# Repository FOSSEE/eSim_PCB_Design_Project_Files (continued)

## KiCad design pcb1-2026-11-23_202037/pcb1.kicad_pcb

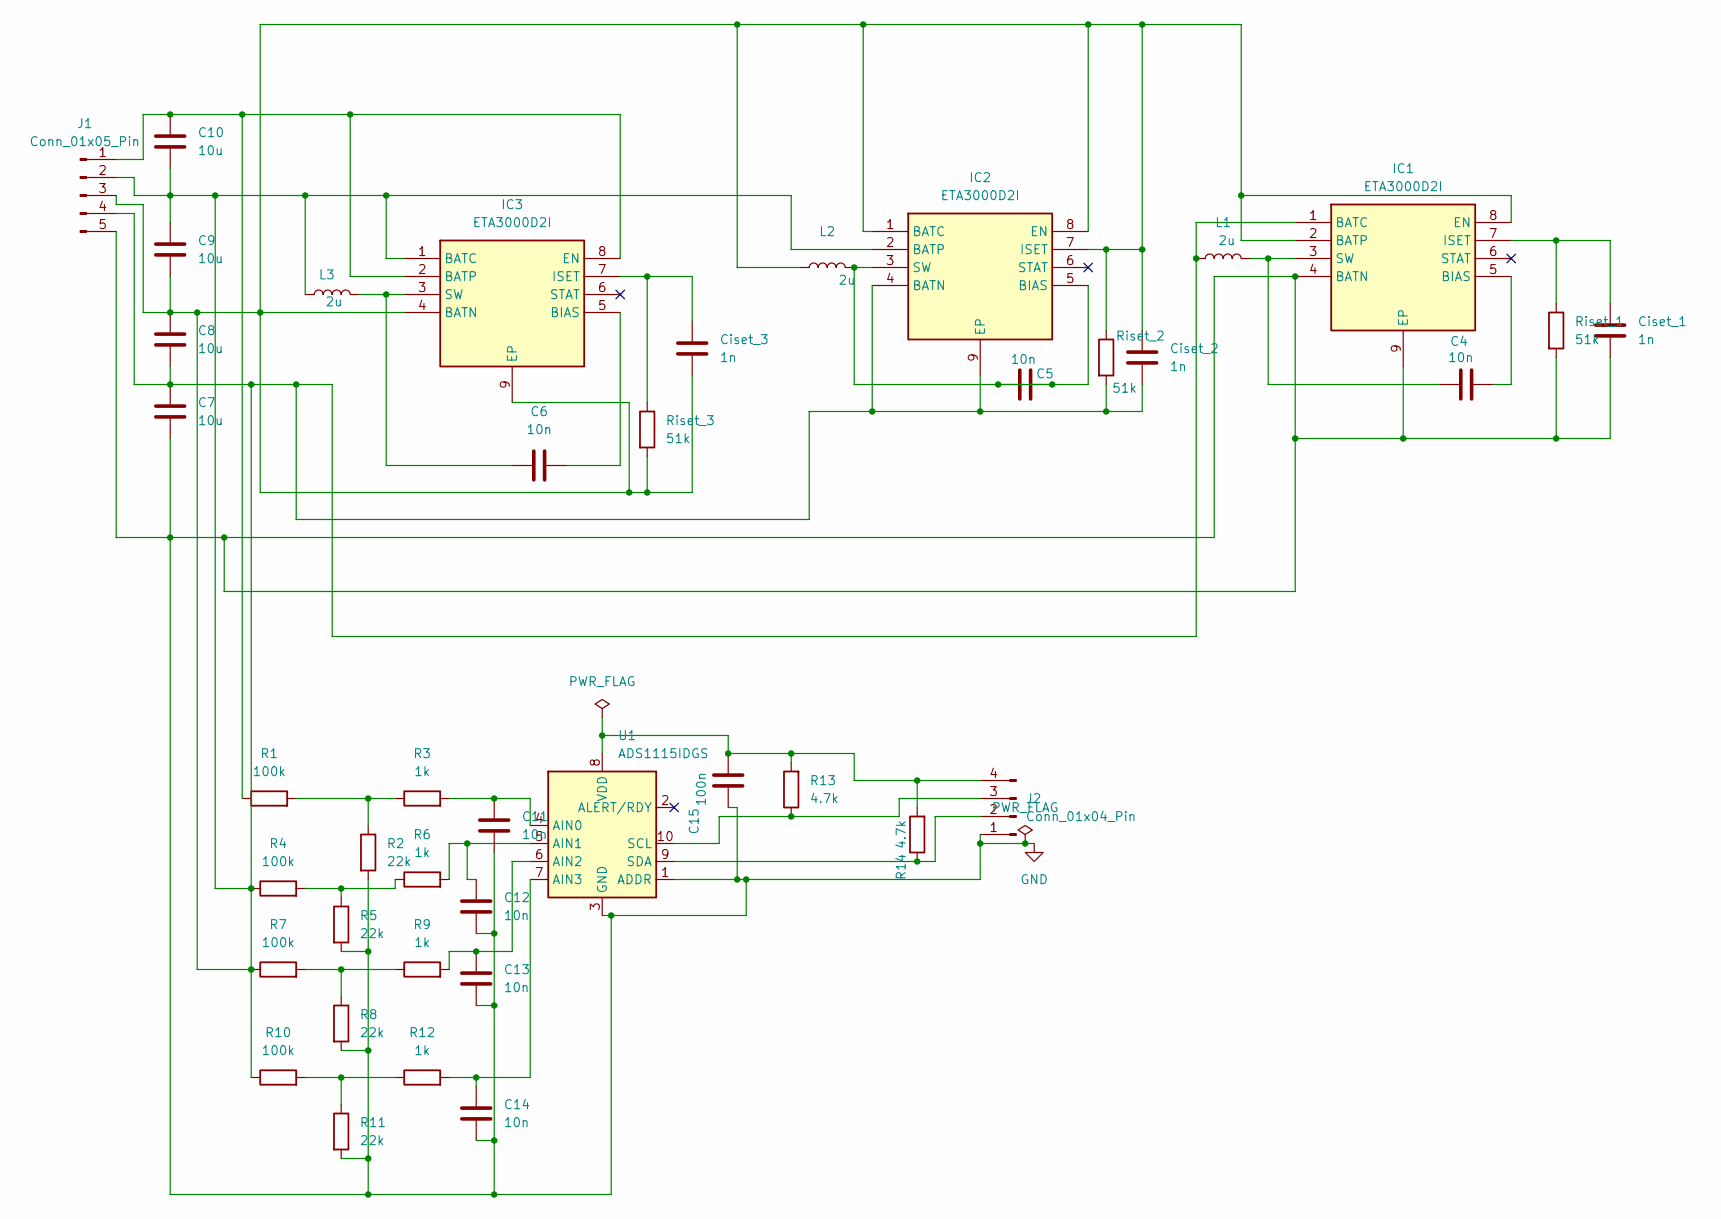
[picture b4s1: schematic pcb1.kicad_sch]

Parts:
C4, C5, C6, C11, C12, C13, C14: 10n; C_0805_2012Metric_Pad1.18x1.45mm_HandSolder
C7, C8, C9, C10: 10u; C_1206_3216Metric_Pad1.33x1.80mm_HandSolder
C15: 100n; C_0805_2012Metric_Pad1.18x1.45mm_HandSolder
Ciset_1, Ciset_2, Ciset_3: 1n; C_0805_2012Metric_Pad1.18x1.45mm_HandSolder
IC1, IC2, IC3: ETA3000D2I; DFN-8-1EP_3x3mm_P0.5mm_EP1.65x2.38mm; Manufacturer_Part_Number ETA3000D2I
J1: Conn_01x05_Pin; JST_XH_B5B-XH-A_1x05_P2.50mm_Vertical
J2: Conn_01x04_Pin; PinHeader_1x04_P2.54mm_Vertical
L1, L2, L3: 2u; L_Bourns-SRN4018
R1, R4, R7, R10: 100k; R_0805_2012Metric_Pad1.20x1.40mm_HandSolder
R2, R5, R8, R11: 22k; R_0805_2012Metric_Pad1.20x1.40mm_HandSolder
R3, R6, R9, R12: 1k; R_0805_2012Metric_Pad1.20x1.40mm_HandSolder
R13, R14: 4.7k; R_0805_2012Metric_Pad1.20x1.40mm_HandSolder
Riset_1, Riset_2, Riset_3: 51k; R_0805_2012Metric_Pad1.20x1.40mm_HandSolder
U1: ADS1115IDGS; TSSOP-10_3x3mm_P0.5mm

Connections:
GND: C7.2, C11.1, C12.1, C13.1, C14.1, C15.2, Ciset_1.1, IC1.4 (BATN), IC1.9 (EP), J1.5, J2.1, R2.2, R5.2, R8.2, R11.2, Riset_1.2, U1.1 (ADDR), U1.3 (GND)
unnamed: C7.1, C8.1, C8.2, C9.1, C9.2, C10.2, Ciset_2.1, Ciset_2.2, Ciset_3.2, IC1.1 (BATC), IC1.2 (BATP), IC1.8 (EN), IC2.1 (BATC), IC2.2 (BATP), IC2.4 (BATN), IC2.7 (ISET), IC2.8 (EN), IC2.9 (EP), IC3.1 (BATC), IC3.4 (BATN), IC3.9 (EP), J1.2, J1.3, J1.4, L1.1, L2.1, L3.1, R4.1, R7.1, R10.1, Riset_2.1, Riset_2.2, Riset_3.2
unnamed: C4.2, IC1.5 (BIAS)
unnamed: Ciset_1.2, IC1.7 (ISET), Riset_1.1
unnamed: C4.1, IC1.3 (SW), L1.2
unnamed: C5.1, C5.2, IC2.3 (SW), IC2.5 (BIAS), L2.2
unnamed: C10.1, IC3.2 (BATP), IC3.8 (EN), J1.1, R1.1
unnamed: C6.2, IC3.5 (BIAS)
unnamed: Ciset_3.1, IC3.7 (ISET), Riset_3.1
unnamed: C6.1, IC3.3 (SW), L3.2
unnamed: J2.2, R14.1, U1.9 (SDA)
unnamed: J2.3, R13.1, U1.10 (SCL)
unnamed: C15.1, J2.4, R13.2, R14.2, U1.8 (VDD)
unnamed: R1.2, R2.1, R3.1
unnamed: R4.2, R5.1, R6.1
unnamed: R7.2, R8.1, R9.1
unnamed: R10.2, R11.1, R12.1
unnamed: C11.2, R3.2, U1.4 (AIN0)
unnamed: C12.2, R6.2, U1.5 (AIN1)
unnamed: C13.2, R9.2, U1.6 (AIN2)
unnamed: C14.2, R12.2, U1.7 (AIN3)

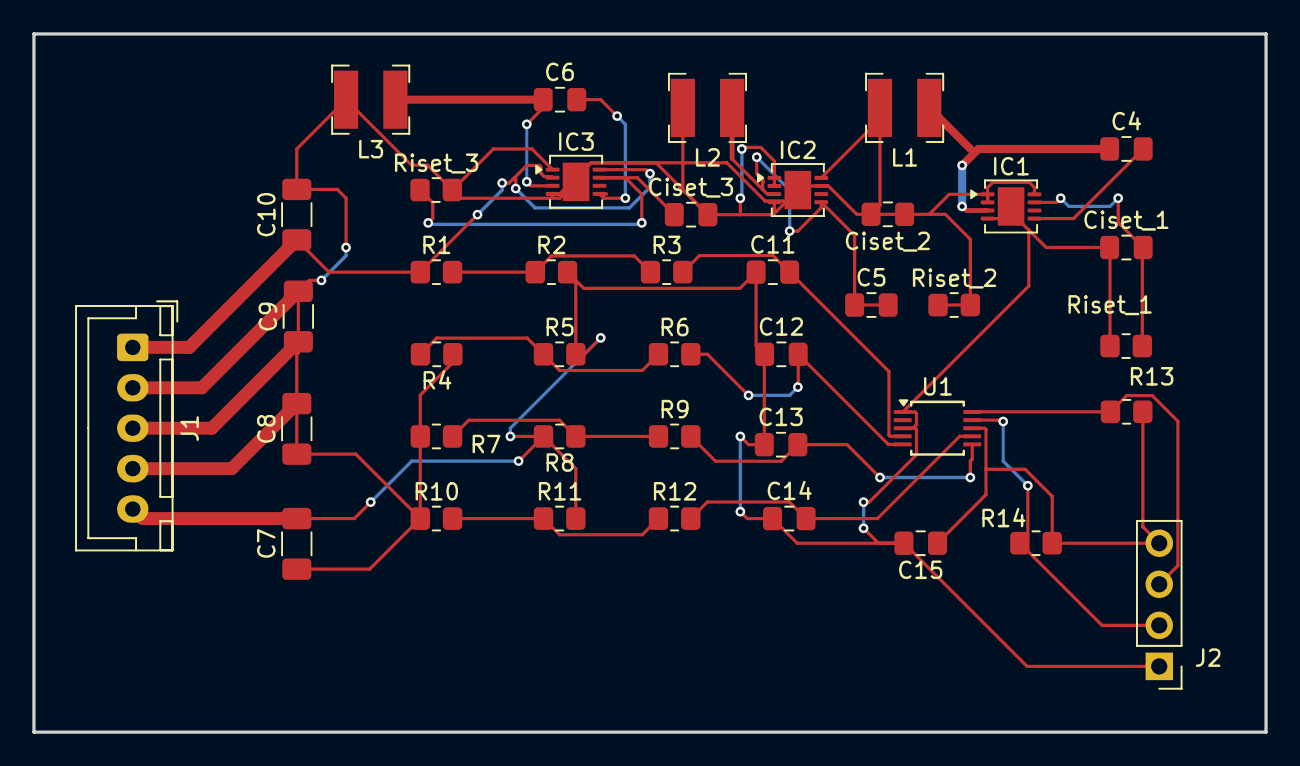
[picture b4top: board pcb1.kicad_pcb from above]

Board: 2 copper layers, 76.2 x 43.2 mm, 41 parts (0 on the bottom side), 21 nets.

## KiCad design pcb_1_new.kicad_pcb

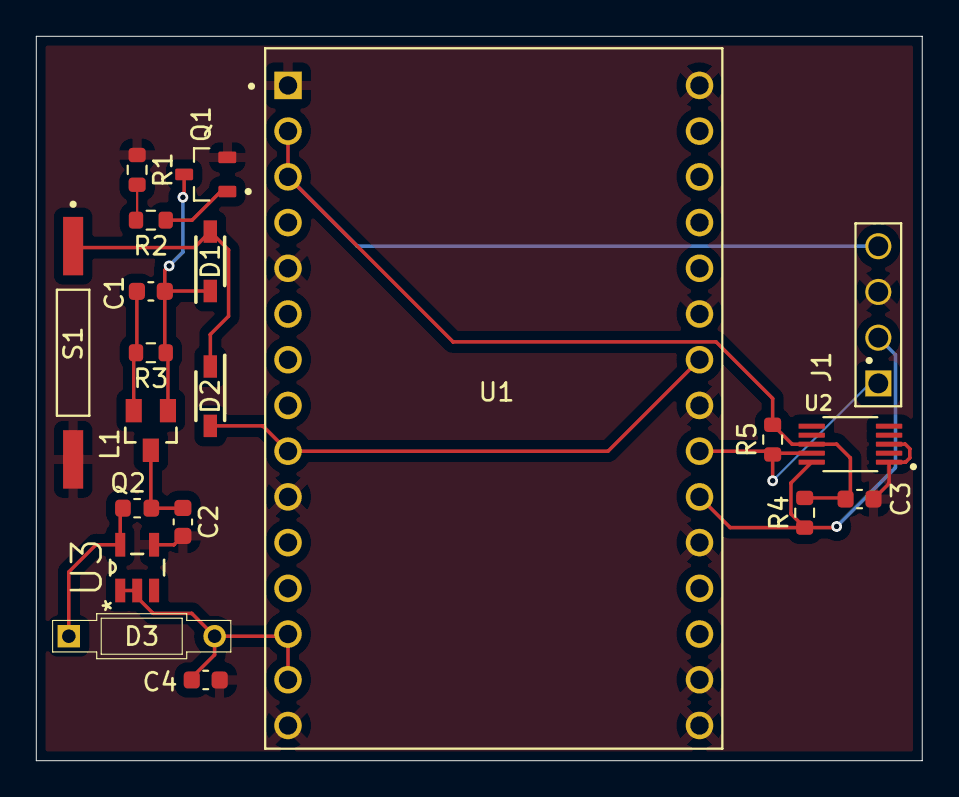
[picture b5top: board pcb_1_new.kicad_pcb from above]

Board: 2 copper layers, 49.2 x 40.2 mm, 20 parts (0 on the bottom side), 13 nets.

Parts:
C1: 100 nF; C_0603_1608Metric
C2: 10uF; C_0603_1608Metric
C3: 0.1uF; C_0603_1608Metric
C4: 47uF; C_0603_1608Metric
D1, D2: 1N4148W-7-F; SOD3716X115N
D3: 1N5711; DIOAD810W51L378D176P
J1: 61300411121; WURTH_61300411121
L1: inductor; L_0603_1608Metric
Q1: MMBT3904; TRANS_MMBT3904
Q2: IRLML6401; SOT23-3
R1, R4, R5: 10K; R_0603_1608Metric
R2: 470; R_0603_1608Metric
R3: 10k; R_0603_1608Metric
S1: MISM7R1015; SW_MISM7R1015
U1: ESP32-C3-DEVKITC-02; XCVR_ESP32-C3-DEVKITC-02
U2: ADS1114IDGSR; SOP50P490X110-10N
U3: NCP1402SN50T1G; SOT95P275X110-5N

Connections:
3V3: C3.1, J1.04, R4.2, R5.2, U1.2 (3V3), U1.3 (3V3), U2.8 (VDD)
Button state pin: D2.2, U1.9 (GPIO7), U1.24 (GPIO10)
GND: C2.2, C3.2, C4.2, J1.03, Q1.2, R1.1, S1.2, U1.1 (GND), U1.5 (GND), U1.10 (GND), U1.15 (GND), U1.16 (GND), U1.17 (GND), U1.20 (GND), U1.23 (GND), U1.25 (GND), U1.30 (GND), U2.1 (ADDR), U2.3 (GND), U3.4 (GND)
unnamed: C1.2, D1.1, Q1.3, Q2.1, R3.1
unnamed: D1.2, D2.1, S1.1
unnamed: D3.1, L1.2, U3.5 (LX)
unnamed: Q1.1, R2.1
POwer hold pin: R1.2, R2.2
SCL: J1.02, R4.1, U1.21 (GPIO21/U0TXD), U2.10 (SCL)
SDA: J1.01, R5.1, U1.22 (GPIO20/U0RXD), U2.9 (SDA)
V5_reg: C4.1, D3.2, U1.13 (5V), U1.14 (5V), U3.1 (CE), U3.2 (OUT)
Vcc: C2.1, L1.1, Q2.3
Vin: C1.1, Q2.2, R3.2

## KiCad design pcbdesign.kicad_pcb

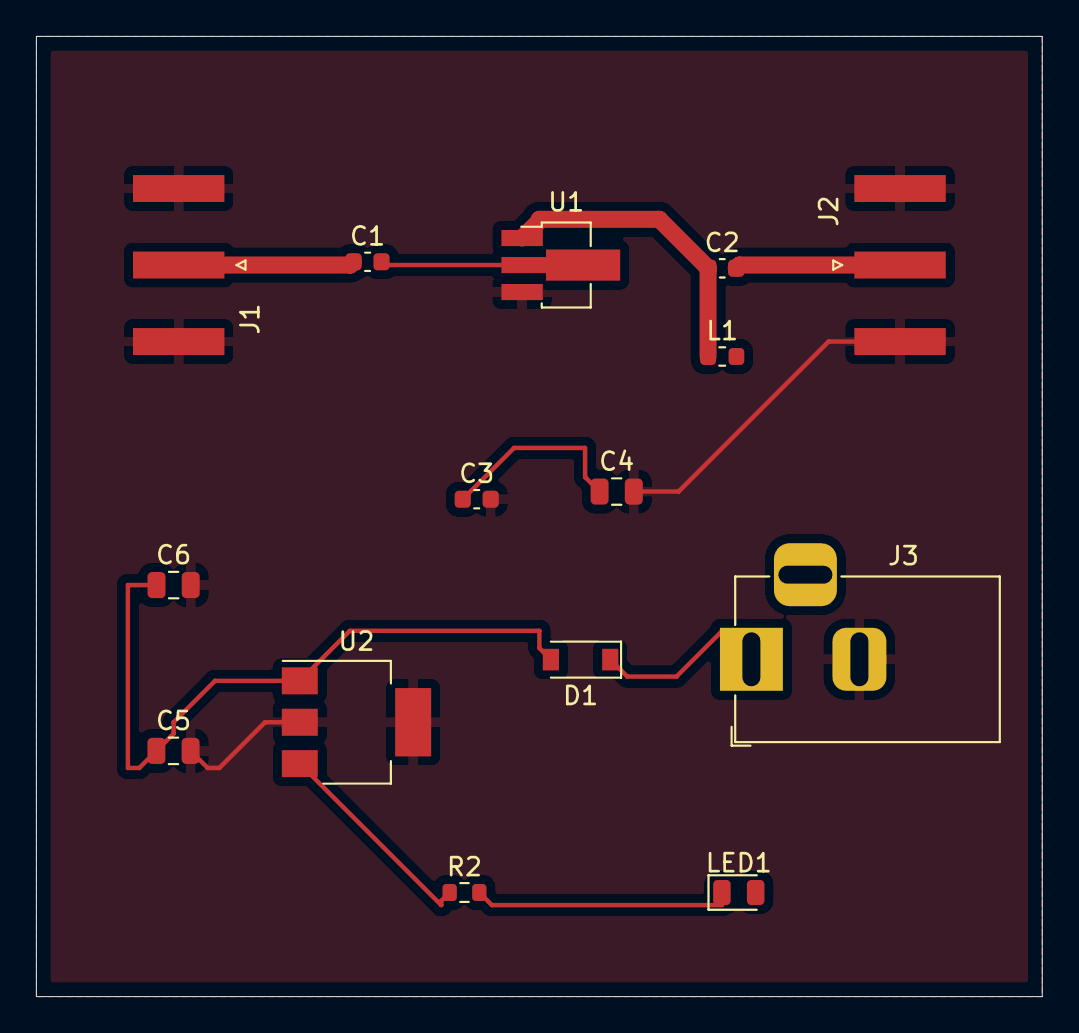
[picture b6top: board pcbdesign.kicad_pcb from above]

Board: 4 copper layers, 55.9 x 53.3 mm, 15 parts (0 on the bottom side), 10 nets.

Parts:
C1, C2, C3: 100pF; C_0603_1608Metric
C4: 100pF; C_0805_2012Metric
C5, C6: 100uF; C_0805_2012Metric
D1: 1N5819; D_SOD-123
J1, J2: eSim_2PinConn; SMA_Amphenol_132289_EdgeMount
J3: eSim_2PinConn; BarrelJack_Horizontal
L1: 47nH; L_0603_1608Metric
LED1: green, 0805; LED_0805_2012Metric
R2: 330; R_0603_1608Metric
U1: SPF5189Z; SOT-89-3_Handsoldering
U2: AMS1117-5.0; SOT-223-3_TabPin2

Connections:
GND: C3.2, C4.2, C5.2, C6.2, J1.2, J2.2, J3.2, U1.3 (E), U2.2
unnamed: C1.1, J1.1
unnamed: C1.2, U1.2 (B)
unnamed: C2.1, L1.1, U1.1 (C)
unnamed: C2.2, J2.1
unnamed: C3.1, C4.1
unnamed: C5.1, C6.1, D1.2 (K), U2.1
unnamed: D1.1 (A), J3.1
unnamed: LED1.1 (A), R2.2
unnamed: R2.1, U2.3

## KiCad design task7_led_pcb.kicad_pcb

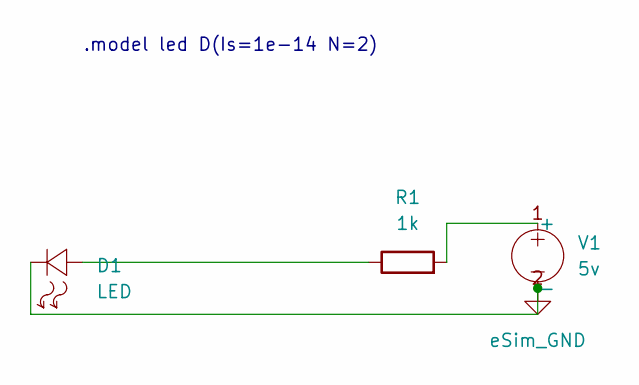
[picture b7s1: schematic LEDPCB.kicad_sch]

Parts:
D1: LED; LED_D5.0mm
R1: 1k; R_Axial_DIN0207_L6.3mm_D2.5mm_P10.16mm_Horizontal
V1: 5v; PinHeader_1x02_P2.54mm_Vertical

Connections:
GND: D1.2 (-), V1.2 (-)
unnamed: D1.1 (+), R1.1
unnamed: R1.2, V1.1 (+)

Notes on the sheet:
.model led D(Is=1e-14 N=2)

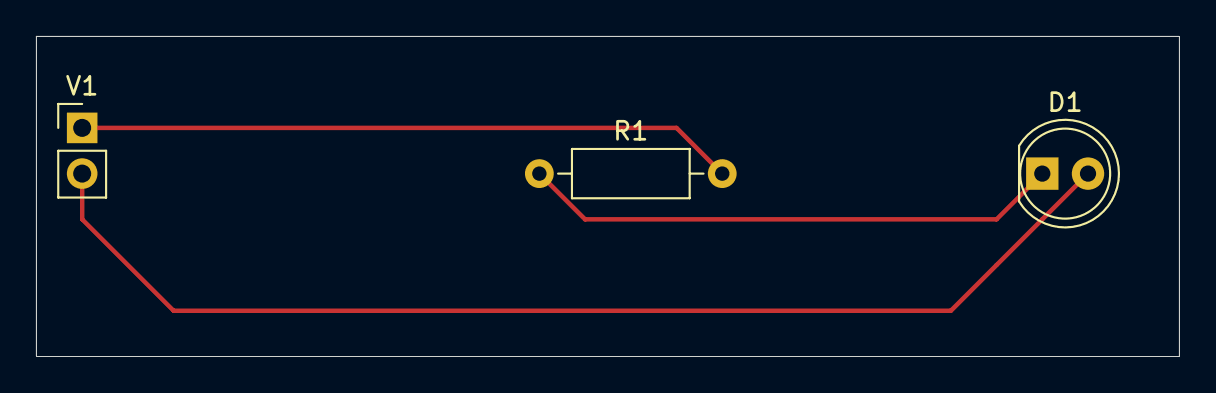
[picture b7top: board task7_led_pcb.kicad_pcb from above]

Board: 2 copper layers, 63.5 x 17.8 mm, 3 parts (0 on the bottom side), 3 nets.

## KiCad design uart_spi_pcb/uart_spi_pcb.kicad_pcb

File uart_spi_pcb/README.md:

# Hardware Implementation and 2-Layer PCB Design of an Asynchronous UART to Synchronous SPI Protocol Bridge Interface Board

**Author:** R. Selvakumaran  
**Affiliation:** Department of Electronics and Communication Engineering, National Institute of Technology Tiruchirappalli (NIT Trichy), Tamil Nadu, India — 620015  
**Host Organization:** Free and Open Source Software for Education (FOSSEE), Indian Institute of Technology Bombay (IIT Bombay)  
**Submission Category:** FOSSEE Semester Long Internship — Autumn 2026 | **Task 7: PCB Design using eSim**  
**EDA Software:** eSim v2.5 / v2.6 (KiCad 6.0.11 Schematic Capture + PCB Editor + 3D Viewer)  
**Date of Completion:** November 23, 2026  

---

## 1. Project Abstract & Overview

This project presents the complete hardware implementation and 2-layer printed circuit board (PCB) design of an autonomous **Universal Asynchronous Receiver-Transmitter (UART) to Serial Peripheral Interface (SPI) Protocol Bridge Interface Board** created strictly using the open-source **eSim EDA** (KiCad backend) suite.

Modern heterogeneous embedded platforms frequently encounter protocol incompatibility when low-speed asynchronous peripherals (UART sensors, GPS units, telemetry links) must interface with high-throughput synchronous bus devices (SPI flash, graphical LCDs, digital signal processors). Conventional solutions rely on software bit-banging on a host microcontroller, introducing severe interrupt latencies, jitter, and excessive CPU utilization. 

This design implements a **hardware-level protocol converter** using discrete 74xx-series high-speed CMOS logic:
1. **Asynchronous Deserializer & Output Latch (U3 - 74HC595):** Captures the incoming asynchronous serial bitstream on `RX` at baud clock edges, shifts bits into an 8-bit SIPO register, and latches the completed byte.
2. **Clock Divider & SPI Frame Controller (U1 - 74HC74):** A dual positive-edge D-flip-flop that prescales the input master clock and generates the autonomous active-low Chip Select (`/CS`) framing signal.
3. **Glitch-Free Gated SPI Clock Generator (U2 - 74LS08):** High-speed 2-input positive AND logic gating the synthesized serial clock with the `/CS` transmission window, guaranteeing compliance with **SPI Mode 0 (`CPOL=0, CPHA=0`)**.
4. **Power Conditioning & Decoupling:** 10 µF electrolytic bulk capacitor (`C1`) and three 100 nF ceramic bypass capacitors (`C2, C3, C4`) placed directly adjacent to IC `VCC`/`GND` pins to suppress high-frequency switching transients and ground bounce.
5. **Diagnostics & Standard Interfacing:** Visual Power LED (`D1`) and SPI Activity LED (`D2`), with standard 2.54 mm pitch vertical headers for 5V DC power (`J1`), UART host (`J2`), and SPI bus (`J3`).

The physical board is realized on a **2-layer rigid FR4 PCB (88.0 mm × 52.0 mm)** with low-impedance ground track chaining and ground plane fill. KiCad's integrated Design Rules Checker (DRC) validates the layout with **0 Violations, 0 Unconnected Items, 0 Errors, and 0 Warnings**.

---

## 2. Hardware Architecture & System Interconnect

```
         +-------------------------------------------------------------+
         |                 5V DC Power Input (J1)                      |
         |                 [+5V, GND] + C1 (10uF) Bulk                 |
         +-------------------------------------------------------------+
                                      |
                                      v
  +--------------------+    +--------------------+    +--------------------+
  |  UART Input (J2)   |    |    74HC595 (U3)    |    |   SPI Output (J3)  |
  |  [VCC, GND, RX,    |--->|  8-Bit SIPO Shift  |--->|  [VCC, GND,        |
  |   Ext CLK]         |    |   Register & Latch |    |   /CS, SCK,        |
  +--------------------+    +--------------------+    |   MOSI, MISO]      |
            |                         ^               +--------------------+
            v                         |                          ^
  +--------------------+              |                          |
  |    74HC74 (U1)     |--------------+                          |
  | Dual D-FF Divider  |-----------------------------------------+
  |  & /CS Controller  |               Gated Burst SCK
  +--------------------+                      ^
            |                                 |
            +------------------------>+----------------+
                                      |  74LS08 (U2)   |
                                      | AND Clock Gate |
                                      +----------------+
```

---

## 3. Bill of Materials (BOM)

| Item | RefDes | Value / Component | Package / Footprint | Qty | Description & Purpose |
|:---:|:---:|:---:|:---:|:---:|:---|
| 1 | U1 | 74HC74 | `Package_DIP:DIP-14_W7.62mm` | 1 | Dual D-type positive-edge flip-flop (clock divider & /CS frame controller) |
| 2 | U2 | 74LS08 | `Package_DIP:DIP-14_W7.62mm` | 1 | Quad 2-input positive-AND gate (SPI Mode 0 gated SCK burst generator) |
| 3 | U3 | 74HC595 | `Package_DIP:DIP-16_W7.62mm` | 1 | 8-bit SIPO shift register with 3-state output storage latch |
| 4 | C1 | 10 µF, 25V | `Capacitor_THT:CP_Radial_D5.0mm_P2.50mm` | 1 | Bulk polarized electrolytic capacitor for input supply ripple smoothing |
| 5 | C2, C3, C4 | 100 nF, 50V | `Capacitor_THT:C_Disc_D3.0mm_W1.6mm_P2.50mm` | 3 | Ceramic disc bypass decoupling capacitors adjacent to IC power pins |
| 6 | R1, R3 | 330 Ω, 0.25W | `Resistor_THT:R_Axial_DIN0207_P7.62mm` | 2 | Current-limiting series resistors for Power LED (D1) and Activity LED (D2) |
| 7 | R2 | 10 kΩ, 0.25W | `Resistor_THT:R_Axial_DIN0207_P7.62mm` | 1 | Pull-up resistor on UART RX line ensuring stable high idle state |
| 8 | D1 | LED Red (PWR) | `LED_THT:LED_D3.0mm` | 1 | 5V DC primary power health indicator |
| 9 | D2 | LED Red (ACT) | `LED_THT:LED_D3.0mm` | 1 | Active SPI transmission burst telemetry indicator |
| 10 | J1 | Conn_01x02 | `Connector_PinHeader_2.54mm:PinHeader_1x02_Vertical` | 1 | Main 5V DC input header (Pin 1: +5V, Pin 2: GND) |
| 11 | J2 | Conn_01x04 | `Connector_PinHeader_2.54mm:PinHeader_1x04_Vertical` | 1 | UART host interface (Pin 1: VCC, Pin 2: GND, Pin 3: RX, Pin 4: CLK) |
| 12 | J3 | Conn_01x06 | `Connector_PinHeader_2.54mm:PinHeader_1x06_Vertical` | 1 | SPI Master header (1: VCC, 2: GND, 3: /CS, 4: SCK, 5: MOSI, 6: MISO) |
| 13 | H1-H4 | MountingHole | `MountingHole:MountingHole_3.2mm_M3` | 4 | M3 mechanical chassis mounting holes at the four board corners |

---

## 4. PCB Specifications & Physical Stackup

- **Board Dimensions:** 88.0 mm × 52.0 mm
- **Board Thickness:** 1.6 mm standard rigid FR4 substrate ($\epsilon_r = 4.5$)
- **Copper Layers:** 2 Copper Layers (1.0 oz / 35 µm copper foil per layer)
  - **Top Copper (`F.Cu` - Red):** Horizontal signal tracks, IC local interconnects, VCC distribution
  - **Bottom Copper (`B.Cu` - Blue):** Vertical orthogonal tracks, low-impedance ground return chaining
- **Track Widths:**
  - Power / Ground Rails (`VCC`, `GND`): **0.50 mm (20 mils)**
  - Digital Logic Signals: **0.25 mm (10 mils)**
- **Clearance Constraints:** 0.25 mm (10 mils) track-to-track; 0.50 mm (20 mils) copper zone clearance
- **Mechanical Mounting:** Four M3 (3.2 mm diameter) unplated holes positioned symmetrically at `(X, Y) = (4.0 mm, 4.0 mm)` from board corners
- **Silkscreen & Solder Mask:** High-contrast white silkscreen over industrial green liquid photo-imageable (LPI) solder mask

---

## 5. Design Rule Check (DRC) Verification

The board was validated using KiCad's integrated **Design Rules Checker (DRC)** with full schematic netlist parity:
- **Violations:** **0**
- **Unconnected Items:** **0**
- **Errors:** **0**
- **Warnings:** **0**

The design has zero unrouted nets, zero clearance violations, and 100% connectivity across all power and signal domains.

---

## 6. How to Open and Inspect the Project in eSim

### Option A: Using eSim GUI
1. Launch **eSim v2.5** (or v2.6).
2. Click **Open Project** and navigate to this directory (`uart_spi_pcb`).
3. Select `uart_spi_pcb.proj` and click **Open**.
4. To view the schematic, click the **Open Schematic** icon (launches eSchema).
5. To view the PCB layout, click the **Open PCB** icon (launches KiCad PCB Editor).
6. In PCB Editor, press **Alt + 3** or navigate to `View -> 3D Viewer` to examine the 3D rendered board.

### Option B: Using Standalone KiCad 6
1. Launch KiCad 6.
2. Open `uart_spi_pcb.kicad_pro`.
3. Open `uart_spi_pcb.kicad_sch` to view and edit the schematic.
4. Open `uart_spi_pcb.kicad_pcb` to view and edit the routed 2-layer layout.
5. In the PCB Editor, navigate to `Inspect -> Design Rules Checker` and click **Run DRC** to confirm **0 Errors, 0 Warnings, 0 Unconnected Items**.

---

## 7. Deliverable File Structure

```
uart_spi_pcb/
│
├── uart_spi_pcb.kicad_sch           # Complete eSchema circuit schematic
├── uart_spi_pcb.kicad_pcb           # 2-layer routed PCB layout file
├── uart_spi_pcb.kicad_pro           # KiCad 6 master project definition file
├── uart_spi_pcb.kicad_prl           # KiCad project local settings file
├── uart_spi_pcb.proj                # eSim project descriptor
├── fp-info-cache                    # Footprint library cache
│
├── UART_to_SPI_Hardware_PCB_Report.pdf  # Comprehensive 11-page technical report
├── README.md                        # Complete project documentation & guide
│
└── Images/                          # High-resolution publication figures
    ├── fig1_circuit_schematic.png           # Schematic capture in eSchema
    ├── fig2_footprint_assignment.jpg        # Footprint assignment dialog
    ├── fig3_pcb_floorplan_silkscreen.png    # Floorplan, Edge.Cuts & silkscreen
    ├── fig4_pcb_routed_2layer_layout.png    # 2-layer routed copper layout
    ├── fig5_drc_validation_zero_errors.png  # DRC report (0 errors, 0 unconnected)
    ├── fig6_3d_viewer_isometric_render.png  # Photorealistic 3D isometric view
    └── fig7_3d_viewer_routed_traces.png     # 3D view of copper traces & annular rings
```

---

## 8. Author Declaration & Compliance

I, **R. Selvakumaran**, hereby declare that this project, submitted for **Task 7: PCB Design using eSim** of the FOSSEE Winter Internship 2026 at the Indian Institute of Technology Bombay (IIT Bombay), is an authentic, original work executed independently by me using eSim and KiCad. All schematics, footprint selections, routing strategies, DRC verifications, and technical documentations were produced directly from my engineering design efforts.

**Contact Details:**
- **Name:** R. Selvakumaran
- **Department:** Electronics and Communication Engineering (2nd Year B.Tech)
- **Institution:** National Institute of Technology Tiruchirappalli (NIT Trichy), Tamil Nadu, India — 620015
- **Submission Destination:** `contact-esim@fossee.in`

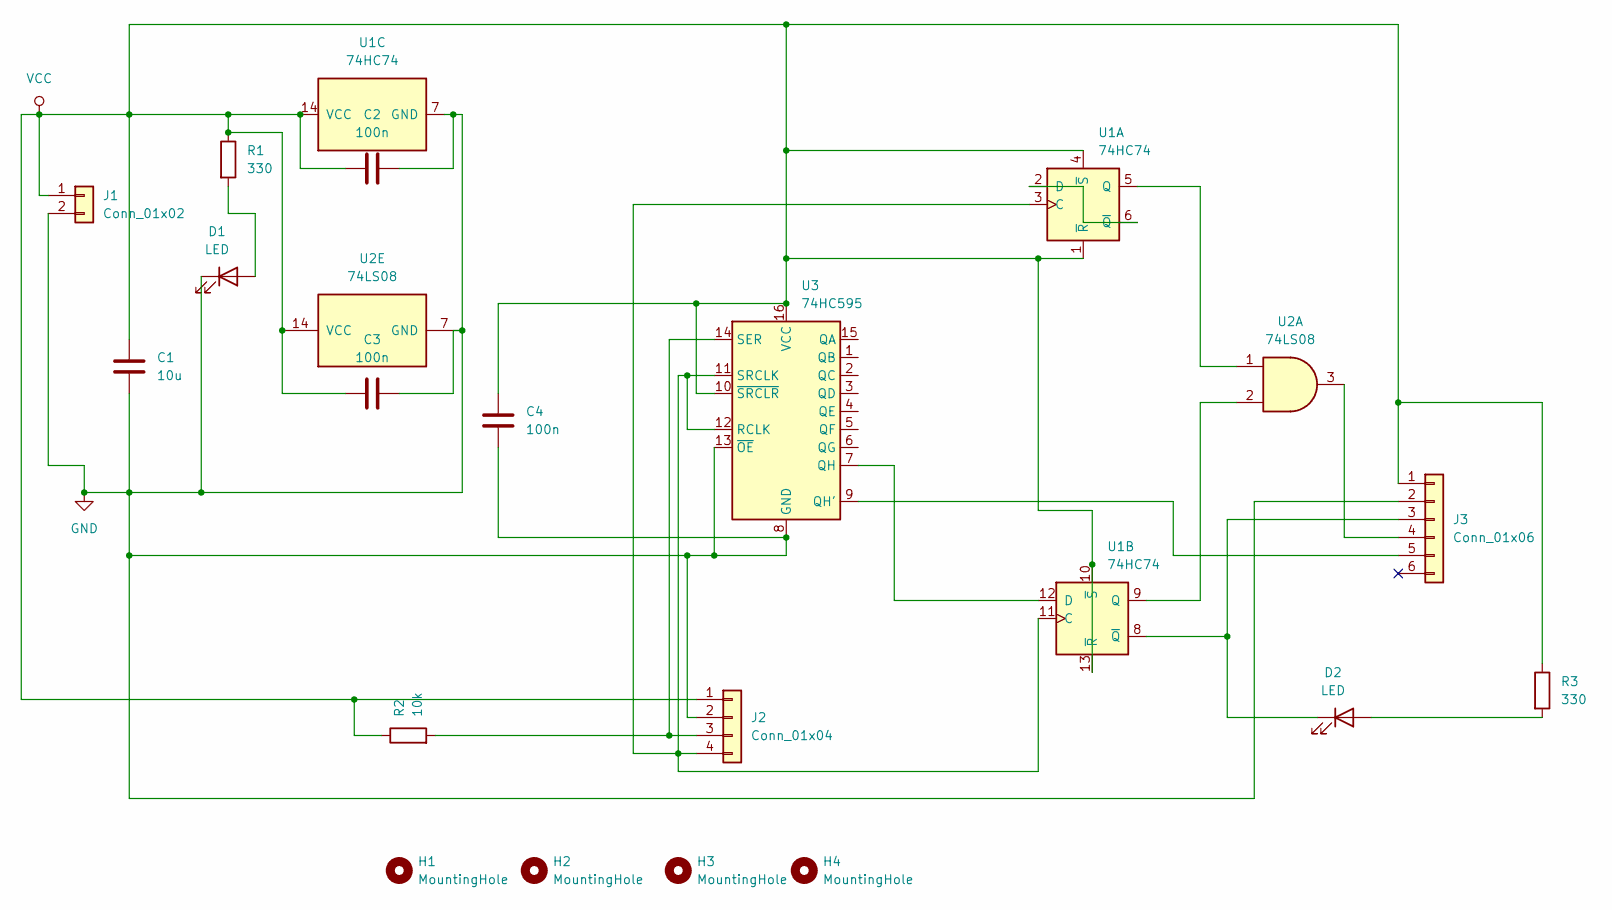
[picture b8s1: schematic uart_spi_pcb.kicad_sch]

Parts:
C1: 10u; CP_Radial_D5.0mm_P2.00mm
C2, C3, C4: 100n; C_Disc_D3.0mm_W2.0mm_P2.50mm
D1, D2: LED; LED_D3.0mm
H1, H2, H3, H4: MountingHole; MountingHole_3.2mm_M3
J1: Conn_01x02; PinHeader_1x02_P2.54mm_Vertical
J2: Conn_01x04; PinHeader_1x04_P2.54mm_Vertical
J3: Conn_01x06; PinHeader_1x06_P2.54mm_Vertical
R1, R3: 330; R_Axial_DIN0207_L6.3mm_D2.5mm_P7.62mm_Horizontal
R2: 10k; R_Axial_DIN0207_L6.3mm_D2.5mm_P7.62mm_Horizontal
U1: 74HC74; DIP-14_W7.62mm
U2: 74LS08; DIP-14_W7.62mm
U3: 74HC595; DIP-16_W7.62mm

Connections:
GND: C1.2, C2.2, C3.2, C4.2, D1.1 (K), J1.2, J2.2, J3.2, U1.7 (GND), U2.7 (GND), U3.8 (GND), U3.13 (~OE)
unnamed: D1.2 (A), R1.2
unnamed: D2.2 (A), R3.2
unnamed: D2.1 (K), J3.3, U1.8 (~Q)
unnamed: J2.3, R2.2, U3.14 (SER)
unnamed: J2.4, U1.3 (C), U1.11 (C), U3.11 (SRCLK), U3.12 (RCLK)
unnamed: J3.4, U2.3
unnamed: J3.5, U3.9 (QH')
unnamed: U1.2 (D), U1.6 (~Q)
unnamed: U1.5 (Q), U2.1
unnamed: U1.12 (D), U3.7 (QH)
unnamed: U1.9 (Q), U2.2
VCC: C1.1, C2.1, C3.1, C4.1, J1.1, J2.1, J3.1, R1.1, R2.1, R3.1, U1.1 (~R), U1.4 (~S), U1.10 (~S), U1.13 (~R), U1.14 (VCC), U2.14 (VCC), U3.10 (~SRCLR), U3.16 (VCC)

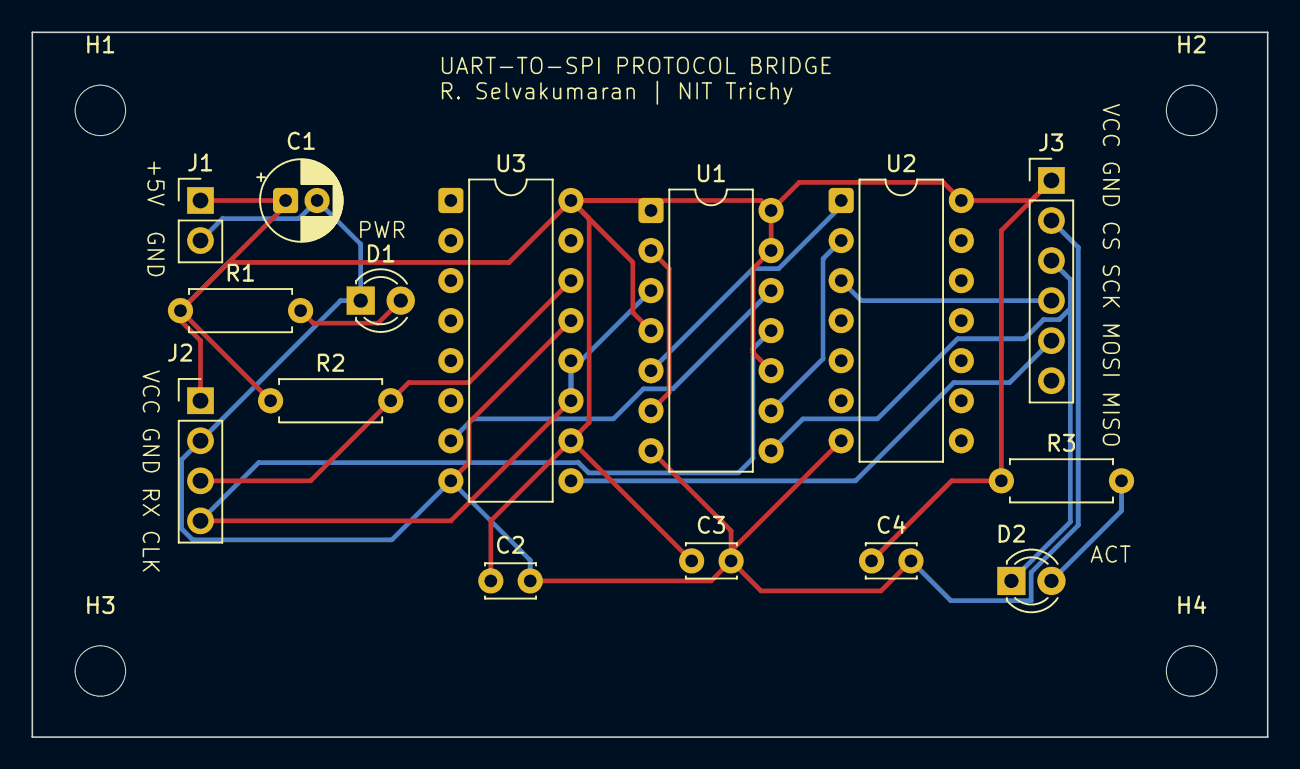
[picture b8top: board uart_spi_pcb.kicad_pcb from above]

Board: 2 copper layers, 78.4 x 44.7 mm, 19 parts (0 on the bottom side), 13 nets.
